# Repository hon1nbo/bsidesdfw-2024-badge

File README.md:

# bsidesdfw-2024-badge
Badge for [BSidesDFW](https://bsidesdfw.com/) and soldering kit for learners! Whilst some experienced hardware folks may think this repo is overkill for a relatively simple badge, the goal is to enable someone to do a fresh start with hardware both in assembly and simple design to try out with KiCAD. Some explanations on choices made are also included to help someone getting started understand why we did things a certain way.

## Assembly
To skip to assembly guidance, we have provided [Instructions](/INSTRUCTIONS.md).

### Badge
If you wanna see the badge in action, there's a GIF of it here (flashing lights warning): [Badge GIF](/images/led-chase.gif)

### Contributors
We're all volunteers doing this in spare time; thanks to those that helped out
- ibi5 - concept & artwork
- BearsInPorts - PCB silkscreen art
- hon1nbo - circuit design, PCB Layout

## Theory of Operation
The theory of operation for this circuit is very simple, as it's primarily intended for learning and practicing soldering. A 555 timer creates a clock signal, adjustable using a trim resistor, which feeds into the serial and clock inputs of a 74hc595 shift register. This shift register takes the serial signal and outputs a set of parallel signals to the LEDs. However, we're not really using serial data but just shifting the on/off position to the next LED in the sequence. As a note, we're using the 74xxx shift register as a Sink for the LED power so this requires a tri-state compatible variant which is available for most of the 74xxxxx series.

## EDA

### Schematic

### Software
[KiCAD](https://www.kicad.org/) is an open-source EDA tool for PCB and Schematic design. We highly recommend it to anyone getting started with hardware design. We used the SacSym Library Loader for parts to get usable footprints for all components. [Models](/models) are included in this repo since not every KiCAD installation uses this software default, as well as the extra silkscreen artwork located under [Art](/art). General KiCAD files are located in [KiCAD files](/KiCAD%20files), and for fabrication we have included the [Gerbers](/gerbers).

### Design Choices

#### Power
We didn't bother including any voltage regulators. Since we are using a 6v supply in the form of coin cells, and entirely through hole components, a linear regulator would be a bit inefficient and additionally the other form factors at a decent component cost would be hard for a beginner to solder. Thus to keep things simple, we stuck with using the diode's inherent voltage drop.

The LEDs used do not have a significant drop-off in lumens when chasing, and the battery life is just fine for this application based on testing with off-the-shelf 2032 batteries. 

#### Tri-State 74xxxxx logic
We went with a Tri-State 74 series shift register to simplify things. Normally, one would use the output of pins on these set to High to send out a signal. However, by using a tri-state in Sink mode (LEDs power goes to the shift register, then to ground), we were able to have a higher overall current limit across the chip. This allowed us to avoid including drive transisitors for all the LEDs and keep things simpler, and allow us to use brighter LEDs. The downside is the chip cost was ever so slightly higher than a standard 74hc595 variant.

#### Errata
AKA: Screw Ups and weird stuff

- One LED (top left front side) is out of place for the badges issued at BSides due to a shifting error from a trace re-route caused when adjusting a pad size on another component to make an unrelated tab easier to solder. The shift was not caught until after fabrication started, but it has been fixed in the KiCAD files.
- Silkscreen for LEDs is on the back. This saves the headache of multi-colour silkscreen or removing the aesthetic of the front design. We wanted to keep the dots so when unassembled it still keeps the design. The LED orientation is not affected by the silkscreen change.
- Schematic shown above still has the old +6V power taps even though the diode drops voltage. This was caught shortly before bsides; I will remove this errata line when I update that schematic after the event.

## Extra Credits
Thanks [SoberDogs](https://soberdogs.weebly.com/) for the use of the sticker art!

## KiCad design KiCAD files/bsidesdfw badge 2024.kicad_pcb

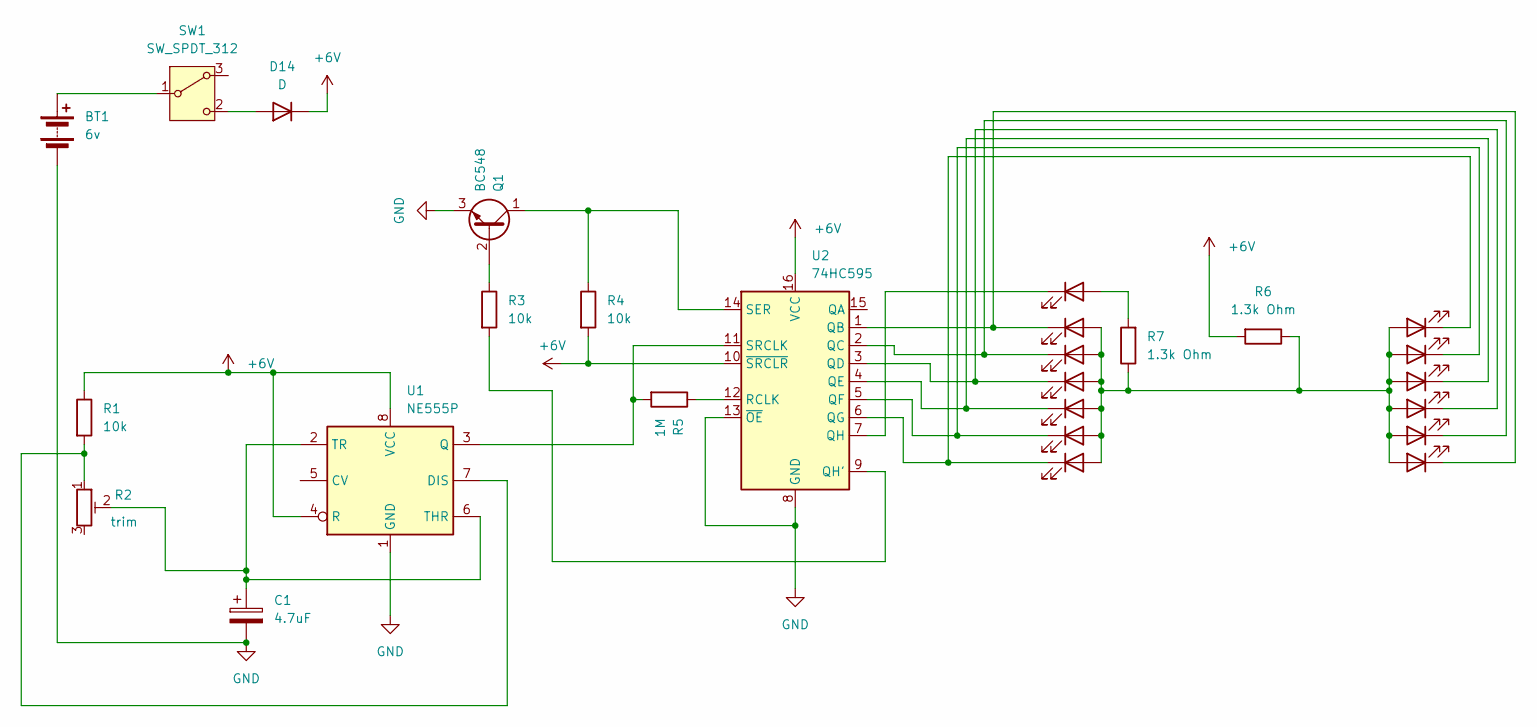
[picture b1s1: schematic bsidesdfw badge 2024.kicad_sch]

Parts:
BT1: 6v; 1062
C1: 4.7uF; CP_Radial_D4.0mm_P1.50mm
D1, D2, D3, D4, D5, D6, D7, D8, D9, D10, D11, D12, D13: LED_D5.0mm
D14: D; D_T-1_P10.16mm_Horizontal
Q1: BC548; TO-92_Inline
R1, R3, R4: 10k; R_Axial_DIN0309_L9.0mm_D3.2mm_P15.24mm_Horizontal
R2: trim; PT10RV10-103A0505-PM-S trim resistor
R5: 1M; R_Axial_DIN0309_L9.0mm_D3.2mm_P15.24mm_Horizontal
R6, R7: 1.3k Ohm; R_Axial_DIN0309_L9.0mm_D3.2mm_P15.24mm_Horizontal
SW1: SW_SPDT_312; SLW12745474ARAD
U1: NE555P; DIP-8_W7.62mm
U2: 74HC595; DIP794W53P254L1930H508Q16N

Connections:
+6V: D14.1 (K), R1.1, R4.2, R6.2, U1.4 (R), U1.8 (VCC), U2.10 (~SRCLR), U2.16 (VCC)
GND: BT1.2 (-), C1.2, Q1.3 (E), U1.1 (GND), U2.8 (GND), U2.13 (~OE)
unnamed: BT1.1 (+), SW1.1 (B)
unnamed: D1.2 (A), D2.2 (A), D3.2 (A), D4.2 (A), D5.2 (A), D6.2 (A), D7.2 (A), D8.2 (A), D9.2 (A), D10.2 (A), D11.2 (A), D12.2 (A), R6.1, R7.1
unnamed: D1.1 (K), D7.1 (K), U2.1 (QB)
unnamed: D2.1 (K), D8.1 (K), U2.2 (QC)
unnamed: D3.1 (K), D9.1 (K), U2.3 (QD)
unnamed: D4.1 (K), D10.1 (K), U2.4 (QE)
unnamed: D5.1 (K), D11.1 (K), U2.5 (QF)
unnamed: D6.1 (K), D12.1 (K), U2.6 (QG)
unnamed: D13.2 (A), R7.2
unnamed: D13.1 (K), U2.7 (QH)
unnamed: D14.2 (A), SW1.2 (C)
unnamed: Q1.2 (B), R3.1
unnamed: Q1.1 (C), R4.1, U2.14 (SER)
unnamed: R1.2, R2.1, U1.7 (DIS)
unnamed: R5.2, U1.3 (Q), U2.11 (SRCLK)
unnamed: C1.1, R2.2, U1.2 (TR), U1.6 (THR)
unnamed: R3.2, U2.9 (QH')
unnamed: R5.1, U2.12 (RCLK)

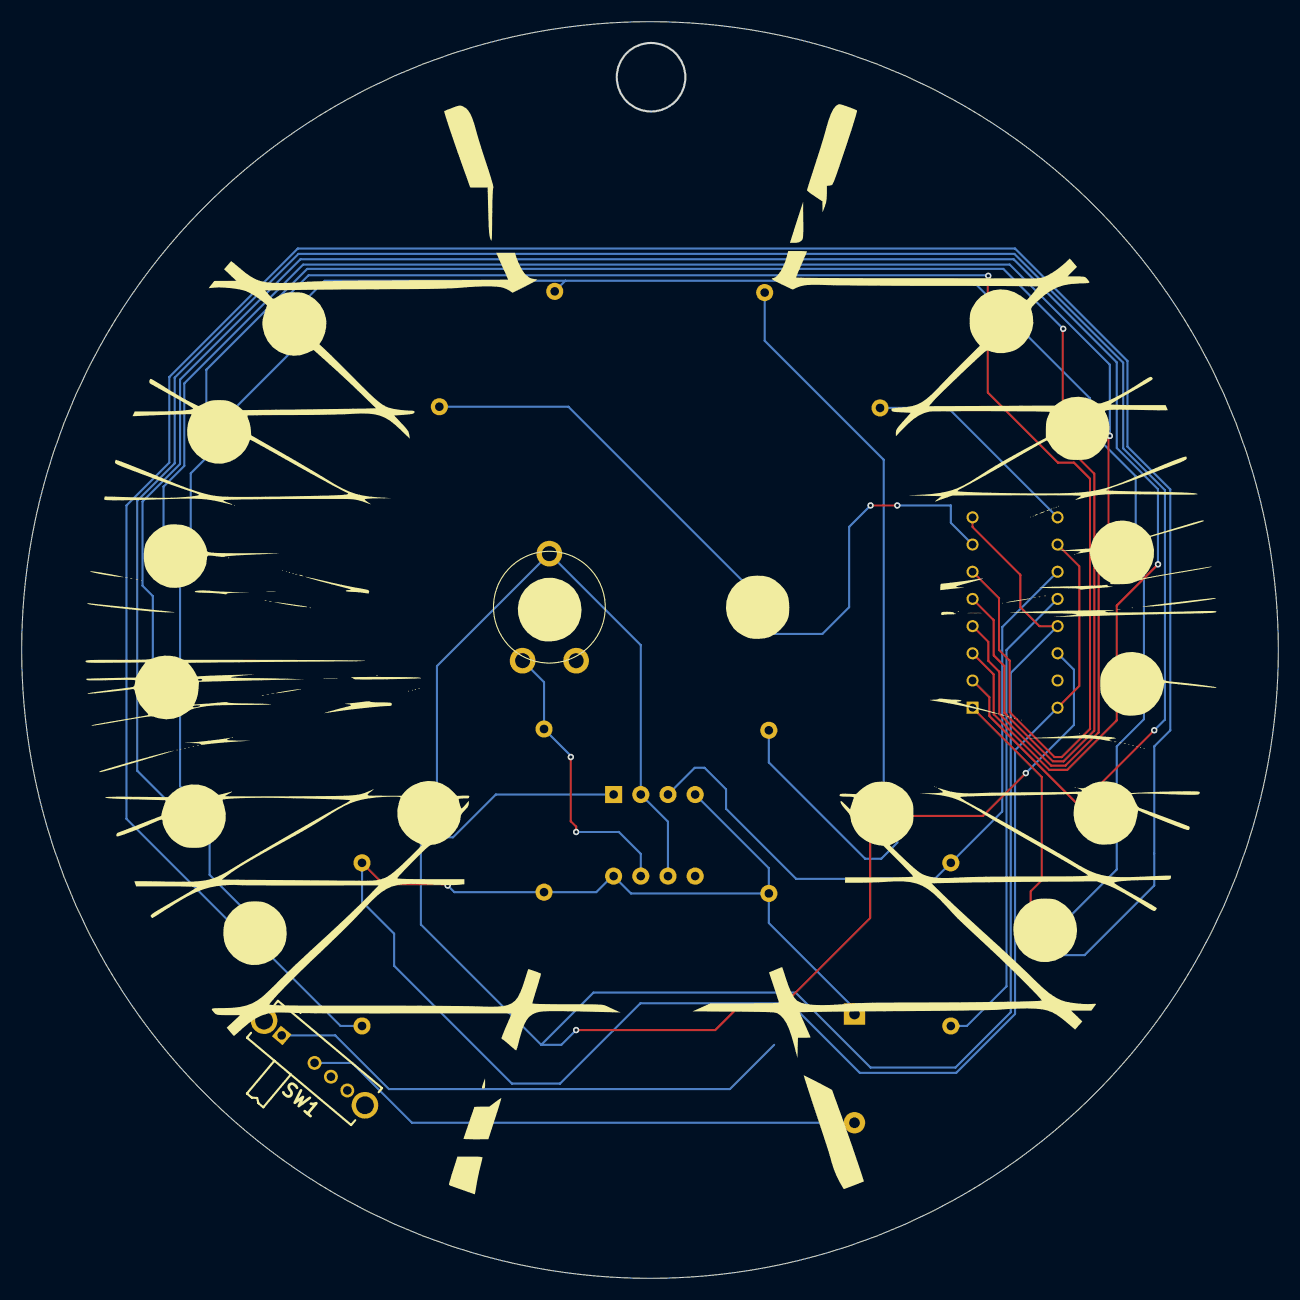
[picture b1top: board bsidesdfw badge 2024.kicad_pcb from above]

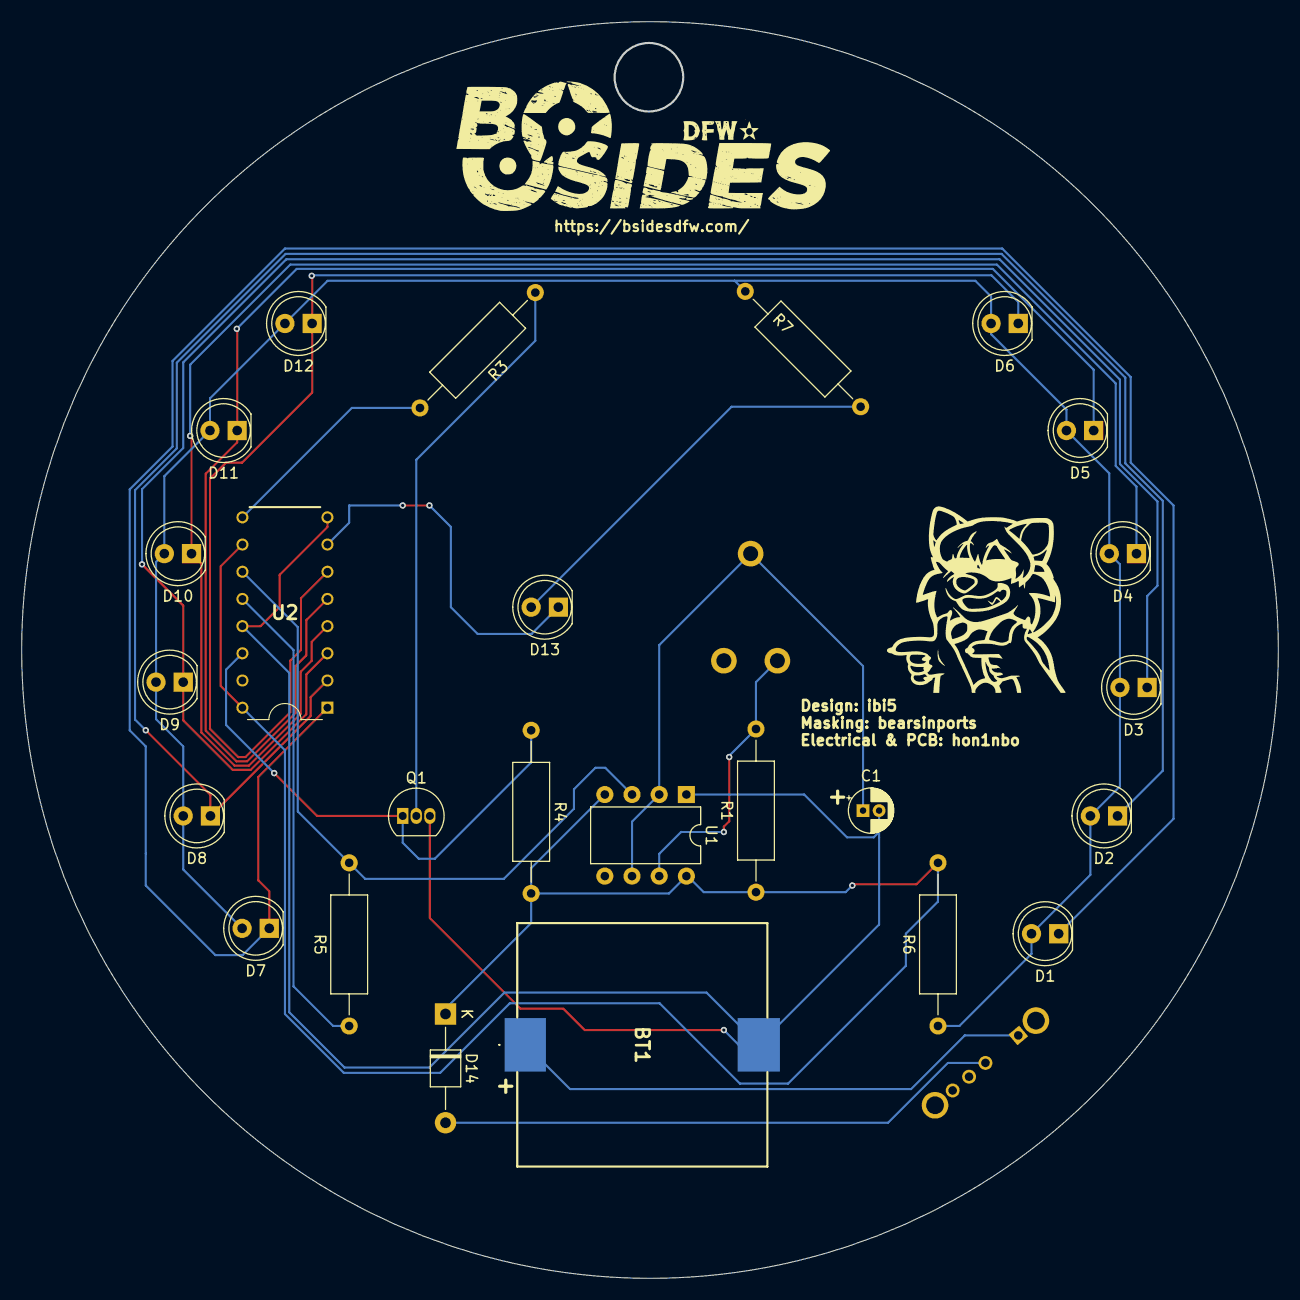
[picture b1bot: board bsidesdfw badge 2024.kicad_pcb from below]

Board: 2 copper layers, 117.2 x 117.2 mm, 27 parts (25 on the bottom side), 20 nets.

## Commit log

2024-09-29 updated number of LEDs
2024-10-01 added initial PCB layout
2024-10-01 LEDs picked, resistor values updated
2024-10-01 README update
2024-10-01 part models. trim pot needs model created
2024-10-01 footprint for trim resistor
2024-10-01 add model for edge power switch
2024-10-01 add some various board footprints to PCB for initial layouts
2024-10-01 corrected the pin numbering for the trim resistor footprint; updated schematic to reflect trim properly
2024-10-01 adjust the 555 drive
2024-10-01 unsure if last changes saved, sending away
2024-10-02 fixed broken footprint assignments; laid out components. Added a diode for reverse polarity protection.
2024-10-02 placement finalized; tentative lanyard hole
2024-10-02 trace rerouting; some silkscreen cleanup. Need to remake the aesthetic mask to fix the dots overlapping the LEDs
2024-10-02 removed dimension that was weirdly in cut layer
2024-10-02 as first test boards were ordered from OSH
2024-10-03 gerbers for PCBWay; Added BSides Logo and website; added silkscreen credits for badge contributors. Moved LED footprints to back of board to address silkscreen conflicts, details are in the README.md
2024-10-04 sync
2024-10-08 prototype badge tested after delivery; to make assembly easier for first timers increasing pad size for battery clip. Adding larger + indicators for some components. Generated new Gerbers
2024-10-08 syncing some saving changes post-plotting; no material changes
2024-10-11 fixed a trace exposure from resizing battery pads; cleaned up and exported schematic to SVG for documentation.
2024-11-01 Errata; cleaned up explanations and some other readme stuff
2024-11-01 add credit to SoberDogs for sticker art used on badge
2024-11-01 README.md cleanup; some file cleanup for extra ZIPs etc that aren't needed
2024-11-02 case sensitivity typo in models link
2024-11-02 GIF of LEDs chasing on the badge
2024-11-02 Update README.md to include Schematic and link to GIF of badge in operation
2024-11-02 Update README. for clarity
2024-11-02 Correct battery holder orientation instructions
2024-11-02 I was slightly wrong, we want to specify that it is the tab itself
2024-11-02 Typo
